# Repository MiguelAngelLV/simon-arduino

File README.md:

Simon Arduino
=============

Simon para Arduino de cuatro colores.

Recuerda que el zumbador debe ir conectado a un pin PWM, si tu modelo de arduino no lo tiene en el PIN 9 selecciona el pin correspondiente la llamada al tone.

El esquema lo tenéis en png y en Fritzing.

Si hay algun problema con los componentes del fichero de la PCB para EAGLE, usa la libreria de Adafruit que se puede descargar en su Github

Se ha cambiado la distribucion de pines original para que la placa sea facilmente routeable a 1 cara.

Si solo quieres realizar la PCB pero no quieres editarla, puedes usar el fichero PDF que contiene el trazado de las pistas y pasarlo a tu placa de la manera que mas te guste.

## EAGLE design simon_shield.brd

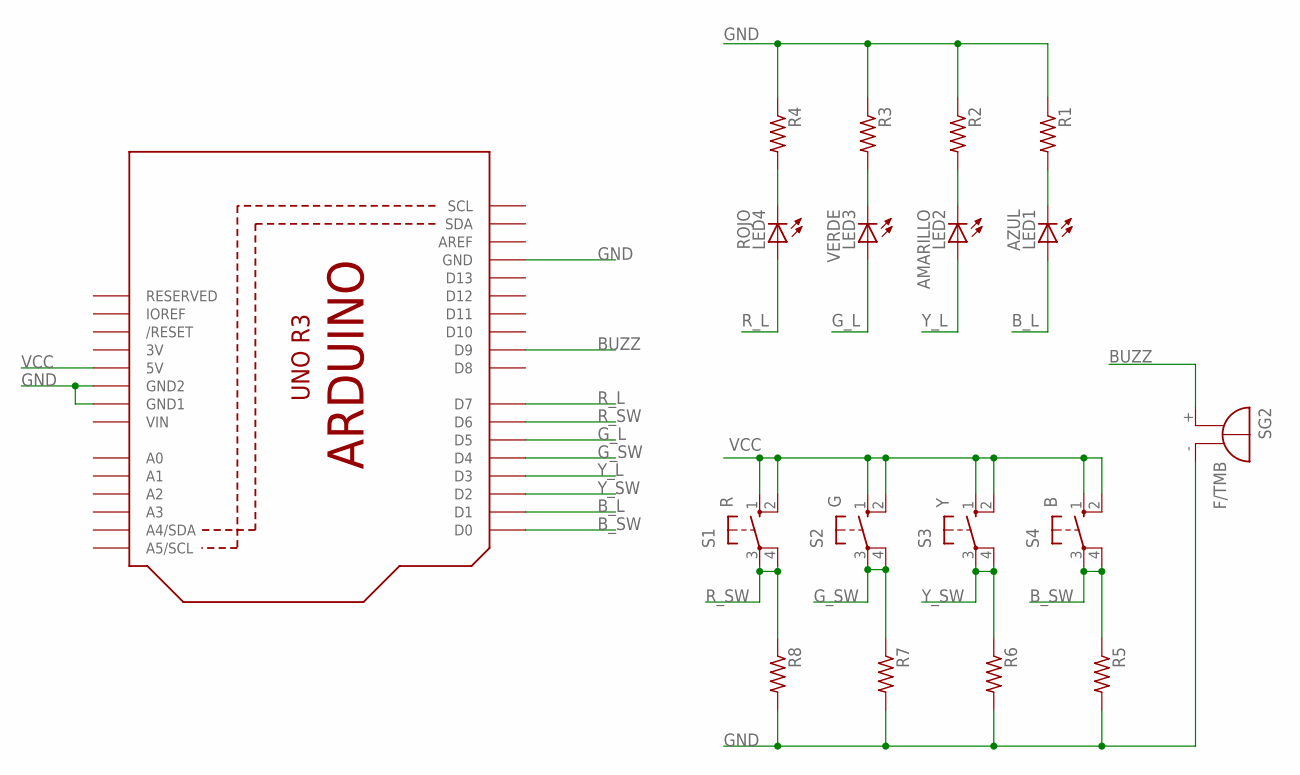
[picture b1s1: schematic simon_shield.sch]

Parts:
LED1: AZUL; LED5MM
LED2: AMARILLO; LED5MM
LED3: VERDE; LED5MM
LED4: ROJO; LED5MM
R1, R2, R3, R4, R5, R6, R7, R8: R-US_0207/10; 0207/10
S1: R; B3F-10XX
S2: G; B3F-10XX
S3: Y; B3F-10XX
S4: B; B3F-10XX
SG2: F/TMB
U1: ARDUINOR3-DIMENSION; ARDUINOR3

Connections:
3V: U1.3V
BUZZ: SG2.+, U1.D9
B_L: LED1.A, U1.D1
B_SW: R5.1, S4.3, S4.4 (P1), U1.D0
GND: R1.1, R2.1, R3.1, R4.1, R5.2, R6.2, R7.2, R8.2, SG2.-, U1.GND, U1.GND1, U1.GND2
G_L: LED3.A, U1.D5
G_SW: R7.1, S2.3, S2.4 (P1), U1.D4
unnamed: LED4.K (C), R4.2
unnamed: LED3.K (C), R3.2
unnamed: LED2.K (C), R2.2
unnamed: LED1.K (C), R1.2
R_L: LED4.A, U1.D7
R_SW: R8.1, S1.3, S1.4 (P1), U1.D6
VCC: S1.1 (S), S1.2 (S1), S2.1 (S), S2.2 (S1), S3.1 (S), S3.2 (S1), S4.1 (S), S4.2 (S1), U1.5V
VIN: U1.VIN
Y_L: LED2.A, U1.D3
Y_SW: R6.1, S3.3, S3.4 (P1), U1.D2

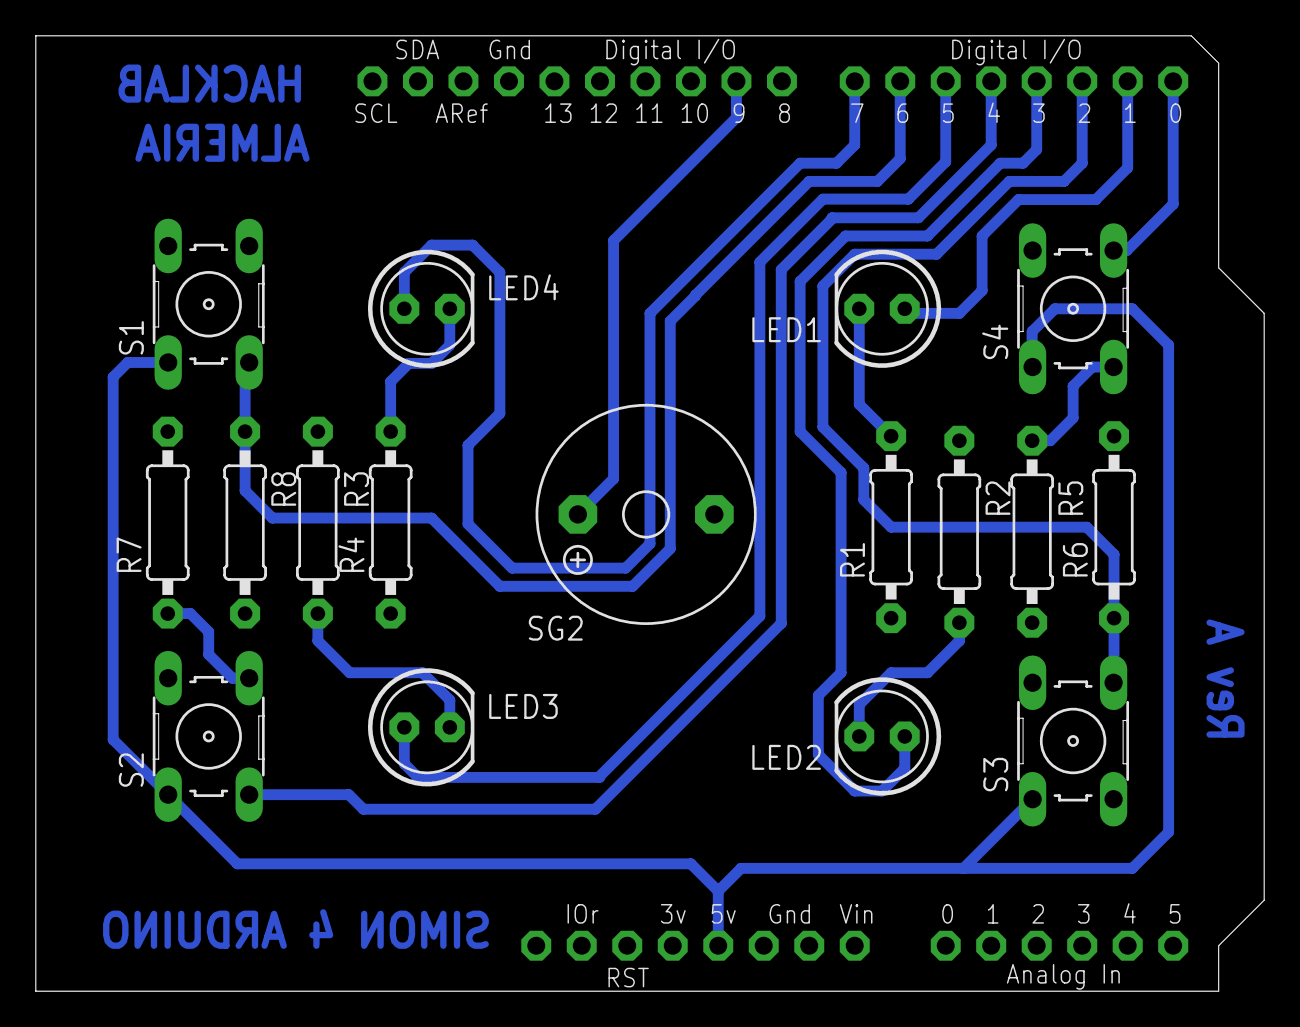
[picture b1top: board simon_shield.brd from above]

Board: 2 copper layers, 68.6 x 53.3 mm, 18 parts (0 on the bottom side), 15 nets.

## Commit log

2014-05-10 Initial
2014-05-14 Añadido escudo para Arduino Uno
    Se ha modificado la distribucion original de pines para los pulsadores y
    led's en el codigo para Arduino, de forma que se pudiera realizar el
    trazado de las pistas facilmente a una cara.
2014-05-26 Create gh-pages branch via GitHub
